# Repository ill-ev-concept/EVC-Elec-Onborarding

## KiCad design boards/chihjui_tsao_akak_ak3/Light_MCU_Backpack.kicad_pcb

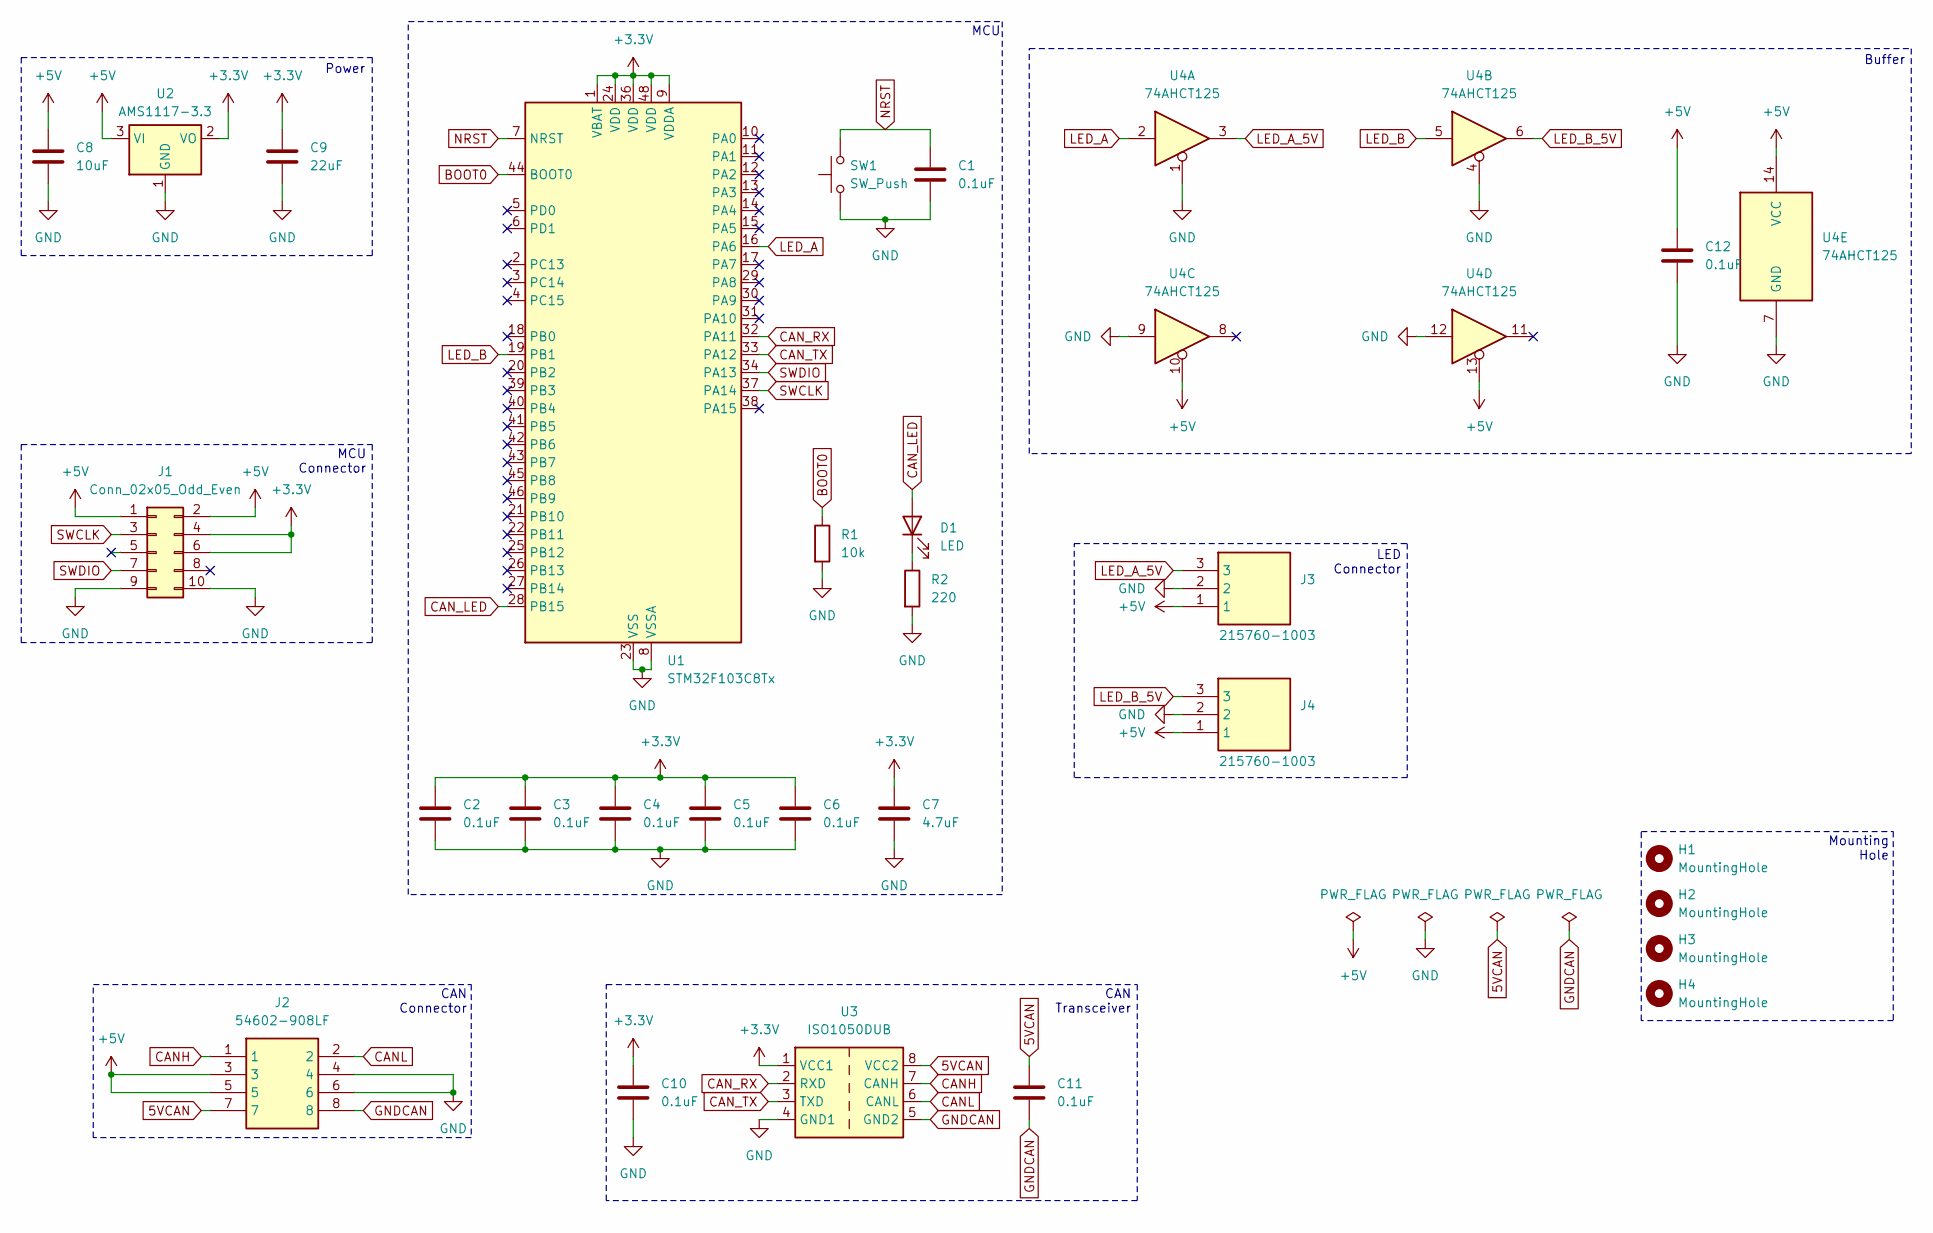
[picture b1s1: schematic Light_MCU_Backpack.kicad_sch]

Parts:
C1, C2, C3, C4, C5, C6, C10, C11, C12: 0.1uF; C_0805_2012Metric
C7: 4.7uF; C_0805_2012Metric
C8: 10uF; C_0805_2012Metric
C9: 22uF; C_0805_2012Metric
D1: LED; LED_0805_2012Metric
H1, H2, H3, H4: MountingHole; MountingHole_3.2mm_M3
J1: Conn_02x05_Odd_Even; PinSocket_2x05_P2.54mm_Vertical
J2: 54602-908LF; 54602908LF; Manufacturer_Part_Number 54602-908LF
J3, J4: 215760-1003; 215760-YY03; Mouser Part Number 538-215760-1003
R1: 10k; R_0805_2012Metric
R2: 220; R_0805_2012Metric
SW1: SW_Push; SW_SPST_EVQQ2
U1: STM32F103C8Tx; LQFP-48_7x7mm_P0.5mm
U2: AMS1117-3.3; SOT-223-3_TabPin2
U3: ISO1050DUB; SOP-8_6.62x9.15mm_P2.54mm
U4: 74AHCT125; SOIC-14_3.9x8.7mm_P1.27mm

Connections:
5VCAN: C11.2, J2.7, U3.8 (VCC2)
+3.3V: C2.1, C3.1, C4.1, C5.1, C6.1, C7.1, C9.2, C10.2, J1.4, J1.6, U1.1 (VBAT), U1.9 (VDDA), U1.24 (VDD), U1.36 (VDD), U1.48 (VDD), U2.2 (VO), U3.1 (VCC1)
+5V: C8.2, C12.1, J1.1, J1.2, J2.3, J2.5, J3.1, J4.1, U2.3 (VI), U4.10, U4.13, U4.14 (VCC)
BOOT0: R1.1, U1.44 (BOOT0)
CANH: J2.1, U3.7 (CANH)
CANL: J2.2, U3.6 (CANL)
CAN_LED: D1.2 (A), U1.28 (PB15)
CAN_RX: U1.32 (PA11), U3.2 (RXD)
CAN_TX: U1.33 (PA12), U3.3 (TXD)
GND: C1.2, C2.2, C3.2, C4.2, C5.2, C6.2, C7.2, C8.1, C9.1, C10.1, C12.2, J1.9, J1.10, J2.4, J2.6, J3.2, J4.2, R1.2, R2.2, SW1.1, U1.8 (VSSA), U1.23 (VSS), U1.35 (VSS), U1.47 (VSS), U2.1 (GND), U3.4 (GND1), U4.1, U4.4, U4.7 (GND), U4.9, U4.12
GNDCAN: C11.1, J2.8, U3.5 (GND2)
LED_A: U1.16 (PA6), U4.2
LED_A_5V: J3.3, U4.3
LED_B: U1.19 (PB1), U4.5
LED_B_5V: J4.3, U4.6
NRST: C1.1, SW1.2, U1.7 (NRST)
unnamed: D1.1 (K), R2.1
SWCLK: J1.3, U1.37 (PA14)
SWDIO: J1.7, U1.34 (PA13)

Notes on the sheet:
Power
CAN Transceiver
CAN Connector
Buffer
MCU Connector
Mounting Hole
LED Connector
MCU

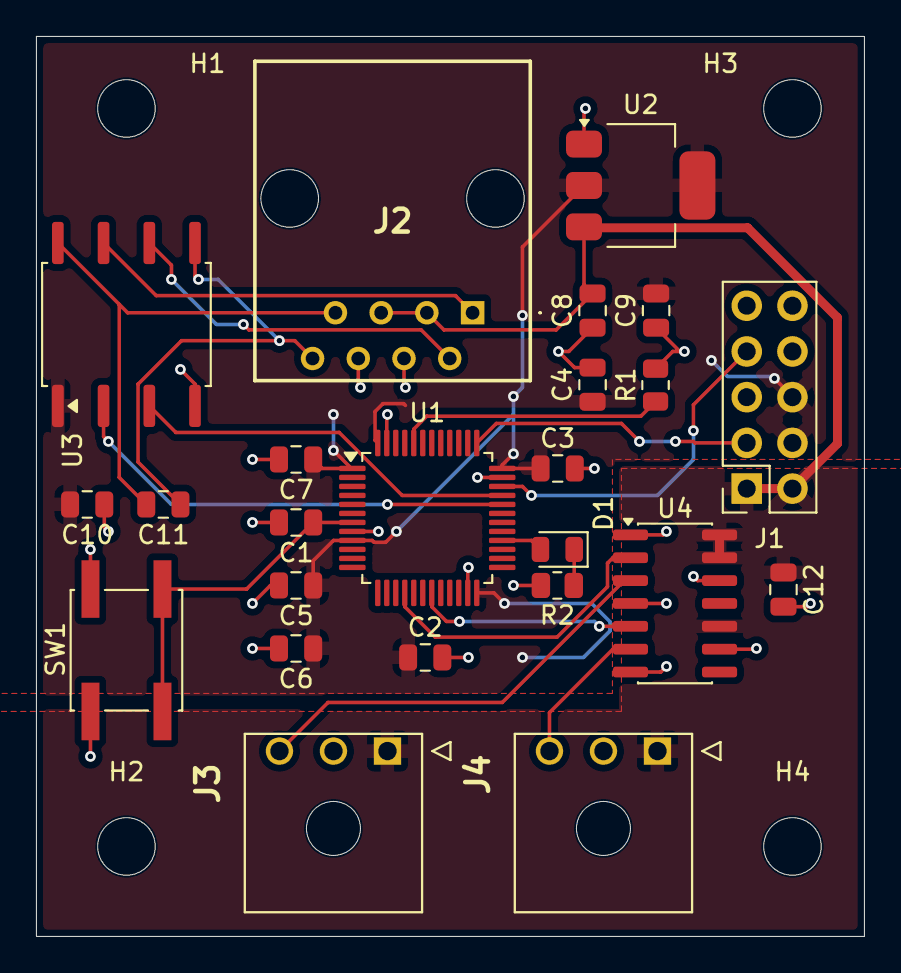
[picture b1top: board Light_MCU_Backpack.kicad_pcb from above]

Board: 2 copper layers, 46.0 x 50.0 mm, 28 parts (0 on the bottom side), 19 nets.

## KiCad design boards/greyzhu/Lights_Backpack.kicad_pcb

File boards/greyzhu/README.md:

# Lights Microcontroller Backpack

Two-layer STM32F103C8T6 board with isolated CAN and two buffered WS2812 interfaces.

| Item | Value |
|---|---|
| Contributor | greyzhu |
| GitHub | saffiotialfredo949-ctrl |
| Discord | grey077913 |
| KiCad | 10.0.6 |
| Board | 100 x 80 mm, two layers, 1.6 mm FR-4 |

## Open the project

Open `Lights_Backpack.kicad_pro` in KiCad. Keep the directory structure intact: the symbol library, footprint library and library tables use `${KIPRJMOD}` paths.

## Contents

- `Lights_Backpack.kicad_sch` and `Lights_Backpack.kicad_pcb`: schematic and routed PCB.
- `Lights_Backpack.pdf`: schematic preview.
- `Backpack.kicad_sym`, `Backpack.pretty/` and library tables: project libraries.
- `BOM.csv`: component list; blank MPN fields require purchasing selection.
- `Component_Positions_Reference.csv`: placement reference in KiCad absolute coordinates.
- `manufacturing/`: nine Gerbers, one Gerber job and two Excellon drill files.
- `ERC_Passed.rpt`, `DRC_Passed.rpt` and `Delivery_Checks.json`: design checks.
- `SHA256SUMS.txt`: file integrity manifest.
- [Hardware guide](HARDWARE_GUIDE.md): interfaces, power limits, fabrication details and initial test procedure.

## Validation and status

Native KiCad ERC reports zero errors and warnings. Native DRC reports zero violations, unconnected pads and footprint errors, with schematic parity enabled. These results apply to the configured checks; the reports list disabled categories.

The design is ready for team review. No prototype has been assembled or tested, and firmware is not included. Before fabrication or assembly, confirm the mating harness pinout, remaining component MPNs and system power budget. Each LED port targets at most 0.4 A before thermal and voltage derating. The CAN side requires an external isolated 5 V supply. J1 uses the custom team programming pinout.

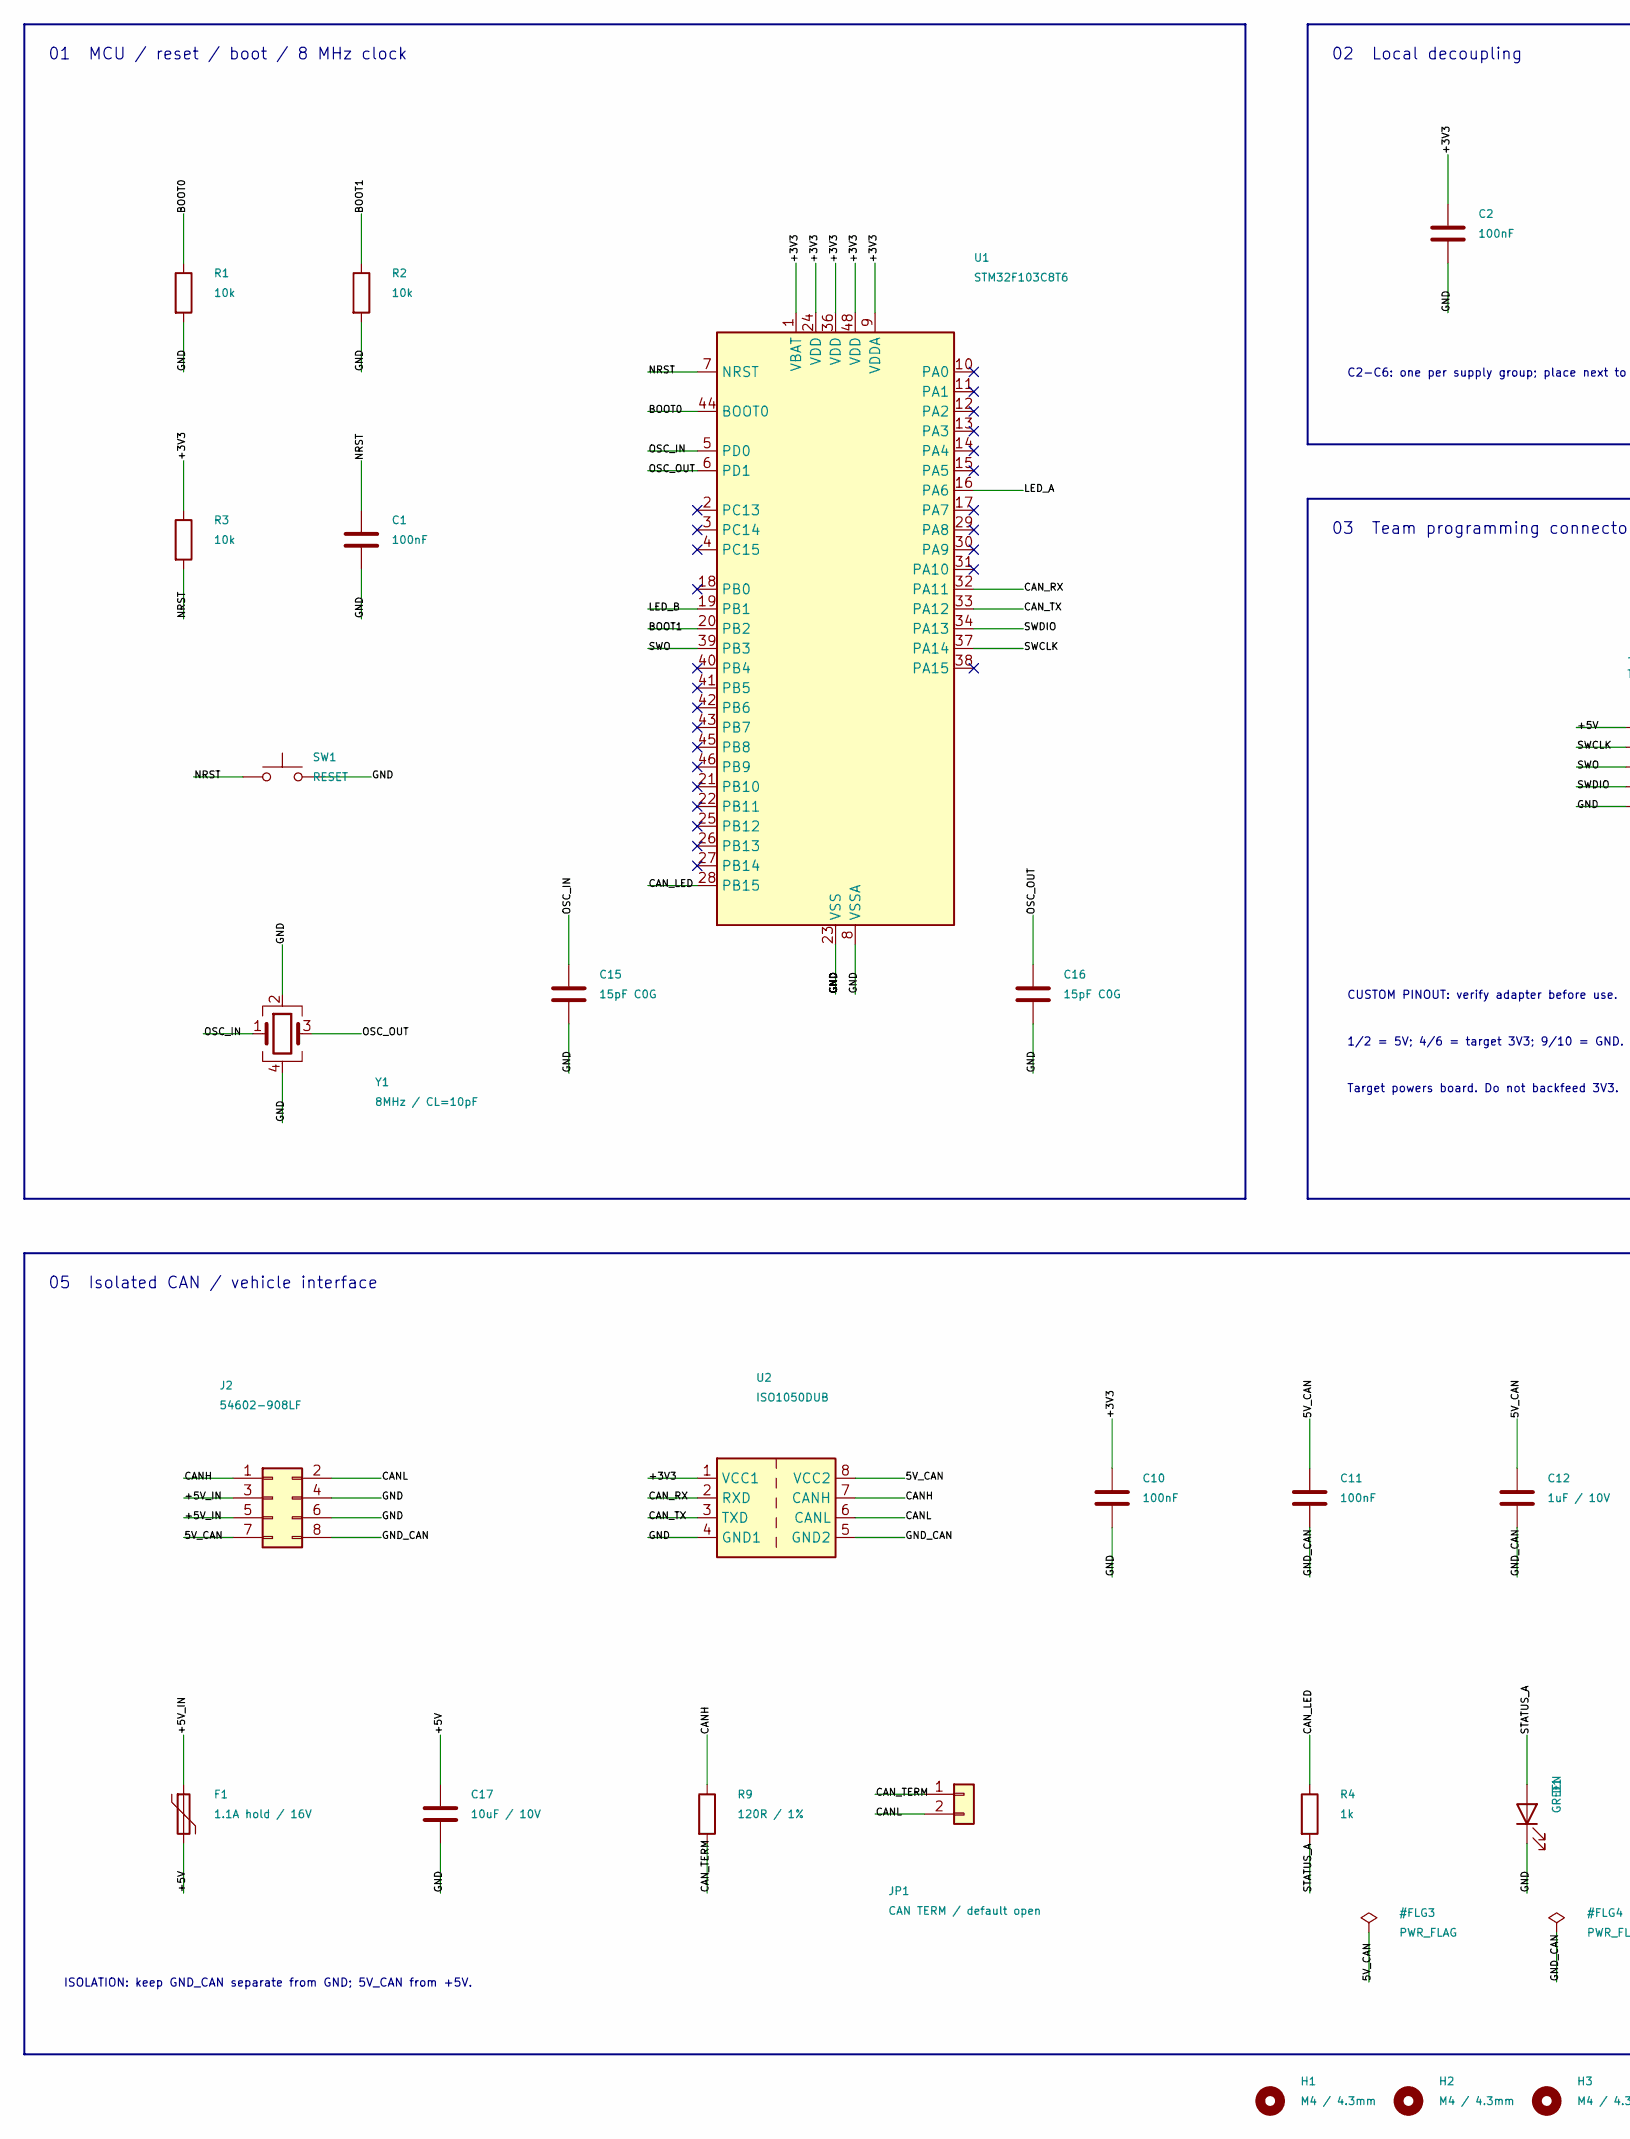
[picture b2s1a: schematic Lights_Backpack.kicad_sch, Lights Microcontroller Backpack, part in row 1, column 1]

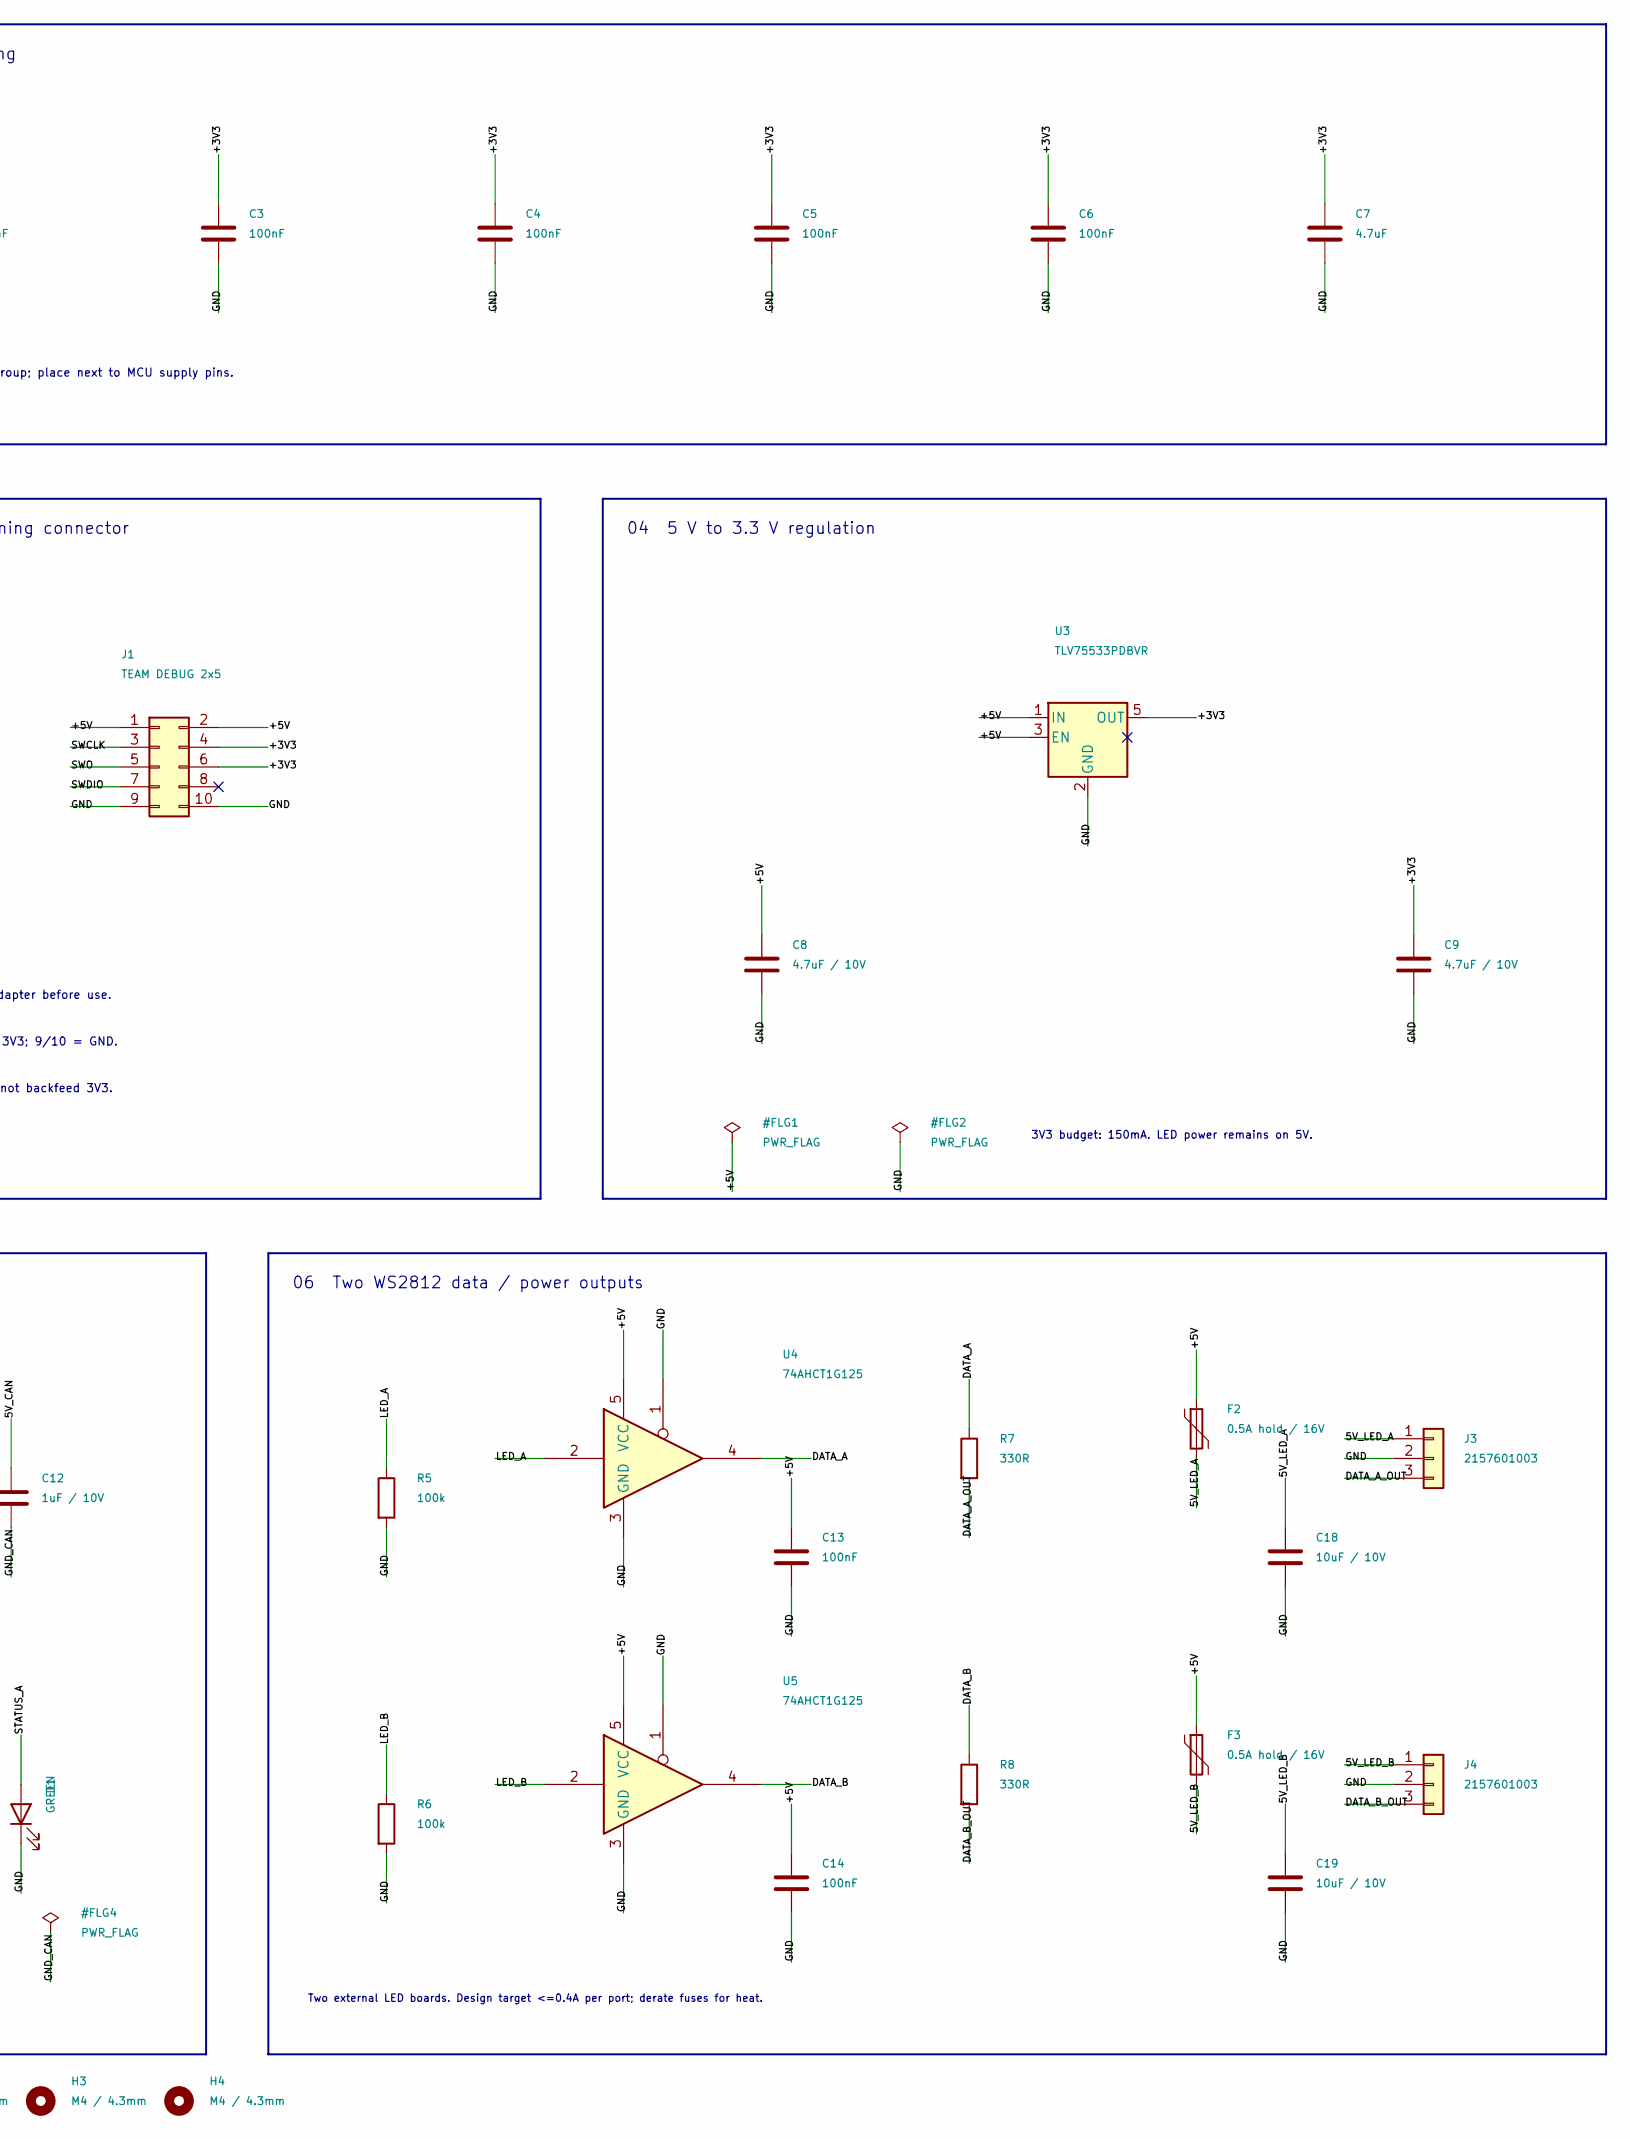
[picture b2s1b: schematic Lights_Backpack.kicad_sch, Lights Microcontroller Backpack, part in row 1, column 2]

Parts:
C1, C2, C3, C4, C5, C6, C10, C11, C13, C14: 100nF; C0603
C7: 4.7uF; C0805
C8, C9: 4.7uF / 10V; C0805
C12: 1uF / 10V; C0805
C15, C16: 15pF C0G; C0603
C17, C18, C19: 10uF / 10V; C0805
D1: GREEN; LED
F1: 1.1A hold / 16V; FUSE; MPN MF-MSMF110/16X-2
F2, F3: 0.5A hold / 16V; FUSE; MPN MF-MSMF050/16X-2
H1, H2, H3, H4: M4 / 4.3mm; HOLE
J1: TEAM DEBUG 2x5; DEBUG
J2: 54602-908LF; RJ45; MPN 54602-908LF
J3, J4: 2157601003; MICROFIT; MPN 2157601003
JP1: CAN TERM / default open; JUMPER
R1, R2, R3: 10k; R0603
R4: 1k; R0603
R5, R6: 100k; R0603
R7, R8: 330R; R0603
R9: 120R / 1%; R0805
SW1: RESET; SW
U1: STM32F103C8T6; MCU; MPN STM32F103C8T6
U2: ISO1050DUB; ISO; MPN ISO1050DUB
U3: TLV75533PDBVR; SOT5; MPN TLV75533PDBVR
U4, U5: 74AHCT1G125; SOT5; MPN SN74AHCT1G125DBVR
Y1: 8MHz / CL=10pF; CRYSTAL; MPN ABM3B-8.000MHZ-10-1-U-T

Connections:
/5V_CAN: C11.1, C12.1, J2.7, U2.8 (VCC2)
/5V_LED_A: C18.1, F2.2, J3.1
/5V_LED_B: C19.1, F3.2, J4.1
/+3V3: C2.1, C3.1, C4.1, C5.1, C6.1, C7.1, C9.1, C10.1, J1.4, J1.6, R3.1, U1.1 (VBAT), U1.9 (VDDA), U1.24 (VDD), U1.36 (VDD), U1.48 (VDD), U2.1 (VCC1), U3.5 (OUT)
/+5V: C8.1, C13.1, C14.1, C17.1, F1.2, F2.1, F3.1, J1.1, J1.2, U3.1 (IN), U3.3 (EN), U4.5 (VCC), U5.5 (VCC)
/+5V_IN: F1.1, J2.3, J2.5
/BOOT0: R1.1, U1.44 (BOOT0)
/BOOT1: R2.1, U1.20 (PB2)
/CANH: J2.1, R9.1, U2.7 (CANH)
/CANL: J2.2, JP1.2, U2.6 (CANL)
/CAN_LED: R4.1, U1.28 (PB15)
/CAN_RX: U1.32 (PA11), U2.2 (RXD)
/CAN_TERM: JP1.1, R9.2
/CAN_TX: U1.33 (PA12), U2.3 (TXD)
/DATA_A: R7.1, U4.4
/DATA_A_OUT: J3.3, R7.2
/DATA_B: R8.1, U5.4
/DATA_B_OUT: J4.3, R8.2
/GND: C1.2, C2.2, C3.2, C4.2, C5.2, C6.2, C7.2, C8.2, C9.2, C10.2, C13.2, C14.2, C15.2, C16.2, C17.2, C18.2, C19.2, D1.1 (K), J1.9, J1.10, J2.4, J2.6, J3.2, J4.2, R1.2, R2.2, R5.2, R6.2, SW1.2, U1.8 (VSSA), U1.23 (VSS), U1.35 (VSS), U1.47 (VSS), U2.4 (GND1), U3.2 (GND), U4.1, U4.3 (GND), U5.1, U5.3 (GND), Y1.2, Y1.4
/GND_CAN: C11.2, C12.2, J2.8, U2.5 (GND2)
/LED_A: R5.1, U1.16 (PA6), U4.2
/LED_B: R6.1, U1.19 (PB1), U5.2
/NRST: C1.1, R3.2, SW1.1, U1.7 (NRST)
/OSC_IN: C15.1, U1.5 (PD0), Y1.1
/OSC_OUT: C16.1, U1.6 (PD1), Y1.3
/STATUS_A: D1.2 (A), R4.2
/SWCLK: J1.3, U1.37 (PA14)
/SWDIO: J1.7, U1.34 (PA13)
/SWO: J1.5, U1.39 (PB3)

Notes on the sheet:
06 Two WS2812 data / power outputs
Target powers board. Do not backfeed 3V3.
02 Local decoupling
01 MCU / reset / boot / 8 MHz clock
1/2 = 5V; 4/6 = target 3V3; 9/10 = GND.
C2-C6: one per supply group; place next to MCU supply pins.
Two external LED boards. Design target <=0.4A per port; derate fuses for heat.
05 Isolated CAN / vehicle interface
04 5 V to 3.3 V regulation
03 Team programming connector
ISOLATION: keep GND_CAN separate from GND; 5V_CAN from +5V.
3V3 budget: 150mA. LED power remains on 5V.
CUSTOM PINOUT: verify adapter before use.

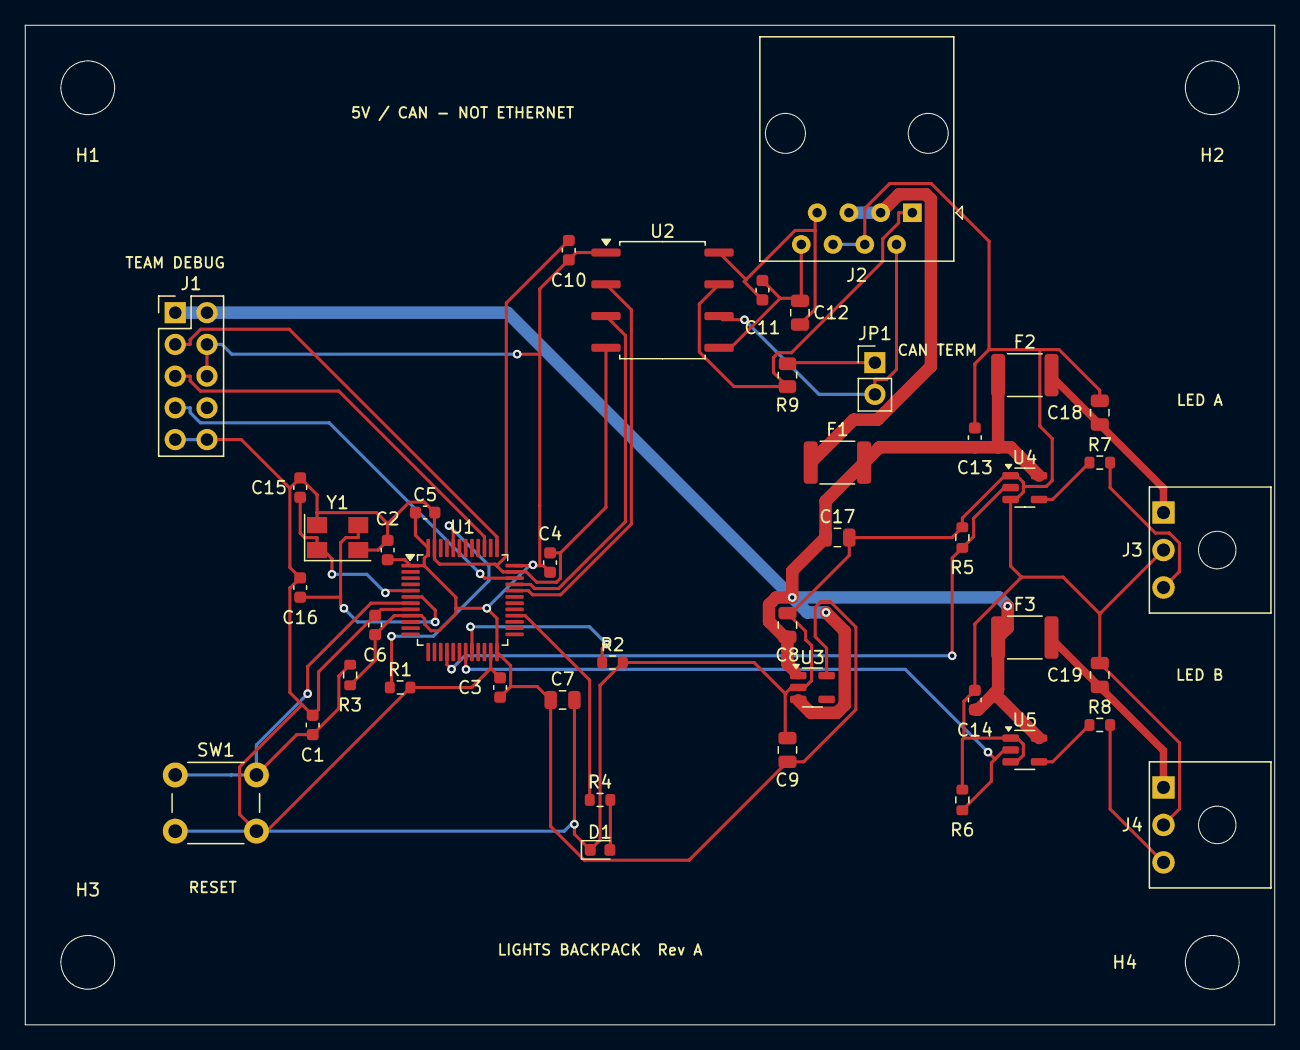
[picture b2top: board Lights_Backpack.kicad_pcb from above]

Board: 2 copper layers, 100.0 x 80.0 mm, 48 parts (0 on the bottom side), 29 nets.

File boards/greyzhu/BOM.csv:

Reference,Quantity,Value,MPN,Footprint,Design note
C1,1,100nF,,Backpack:C0603,
C2,1,100nF,,Backpack:C0603,
C3,1,100nF,,Backpack:C0603,
C4,1,100nF,,Backpack:C0603,
C5,1,100nF,,Backpack:C0603,
C6,1,100nF,,Backpack:C0603,
C7,1,4.7uF,,Backpack:C0805,
C8,1,4.7uF / 10V,,Backpack:C0805,
C9,1,4.7uF / 10V,,Backpack:C0805,
C10,1,100nF,,Backpack:C0603,
C11,1,100nF,,Backpack:C0603,
C12,1,1uF / 10V,,Backpack:C0805,
C13,1,100nF,,Backpack:C0603,
C14,1,100nF,,Backpack:C0603,
C15,1,15pF C0G,,Backpack:C0603,
C16,1,15pF C0G,,Backpack:C0603,
C17,1,10uF / 10V,,Backpack:C0805,
C18,1,10uF / 10V,,Backpack:C0805,
C19,1,10uF / 10V,,Backpack:C0805,
D1,1,GREEN,,Backpack:LED,
F1,1,1.1A hold / 16V,MF-MSMF110/16X-2,Backpack:FUSE,
F2,1,0.5A hold / 16V,MF-MSMF050/16X-2,Backpack:FUSE,
F3,1,0.5A hold / 16V,MF-MSMF050/16X-2,Backpack:FUSE,
H1,1,M4 / 4.3mm,,Backpack:HOLE,4.3mm non-plated mounting hole; keep copper clear.
H2,1,M4 / 4.3mm,,Backpack:HOLE,4.3mm non-plated mounting hole; keep copper clear.
H3,1,M4 / 4.3mm,,Backpack:HOLE,4.3mm non-plated mounting hole; keep copper clear.
H4,1,M4 / 4.3mm,,Backpack:HOLE,4.3mm non-plated mounting hole; keep copper clear.
J1,1,TEAM DEBUG 2x5,,Backpack:DEBUG,Custom team pinout. Not ARM Cortex 10-pin. Do not parallel external 5V sources.
J2,1,54602-908LF,54602-908LF,Backpack:RJ45,"Team vehicle connector, NOT Ethernet. Pinout from assignment."
J3,1,2157601003,2157601003,Backpack:MICROFIT,"Board pinout: 1=5V, 2=GND, 3=DATA. Confirm mating harness."
J4,1,2157601003,2157601003,Backpack:MICROFIT,"Board pinout: 1=5V, 2=GND, 3=DATA. Confirm mating harness."
JP1,1,CAN TERM / default open,,Backpack:JUMPER,Default open. Fit only if this node is one of the two physical bus ends.
R1,1,10k,,Backpack:R0603,
R2,1,10k,,Backpack:R0603,
R3,1,10k,,Backpack:R0603,
R4,1,1k,,Backpack:R0603,
R5,1,100k,,Backpack:R0603,
R6,1,100k,,Backpack:R0603,
R7,1,330R,,Backpack:R0603,
R8,1,330R,,Backpack:R0603,
R9,1,120R / 1%,,Backpack:R0805,
SW1,1,RESET,,Backpack:SW,
U1,1,STM32F103C8T6,STM32F103C8T6,Backpack:MCU,
U2,1,ISO1050DUB,ISO1050DUB,Backpack:ISO,
U3,1,TLV75533PDBVR,TLV75533PDBVR,Backpack:SOT5,
U4,1,74AHCT1G125,SN74AHCT1G125DBVR,Backpack:SOT5,
U5,1,74AHCT1G125,SN74AHCT1G125DBVR,Backpack:SOT5,
Y1,1,8MHz / CL=10pF,ABM3B-8.000MHZ-10-1-U-T,Backpack:CRYSTAL,

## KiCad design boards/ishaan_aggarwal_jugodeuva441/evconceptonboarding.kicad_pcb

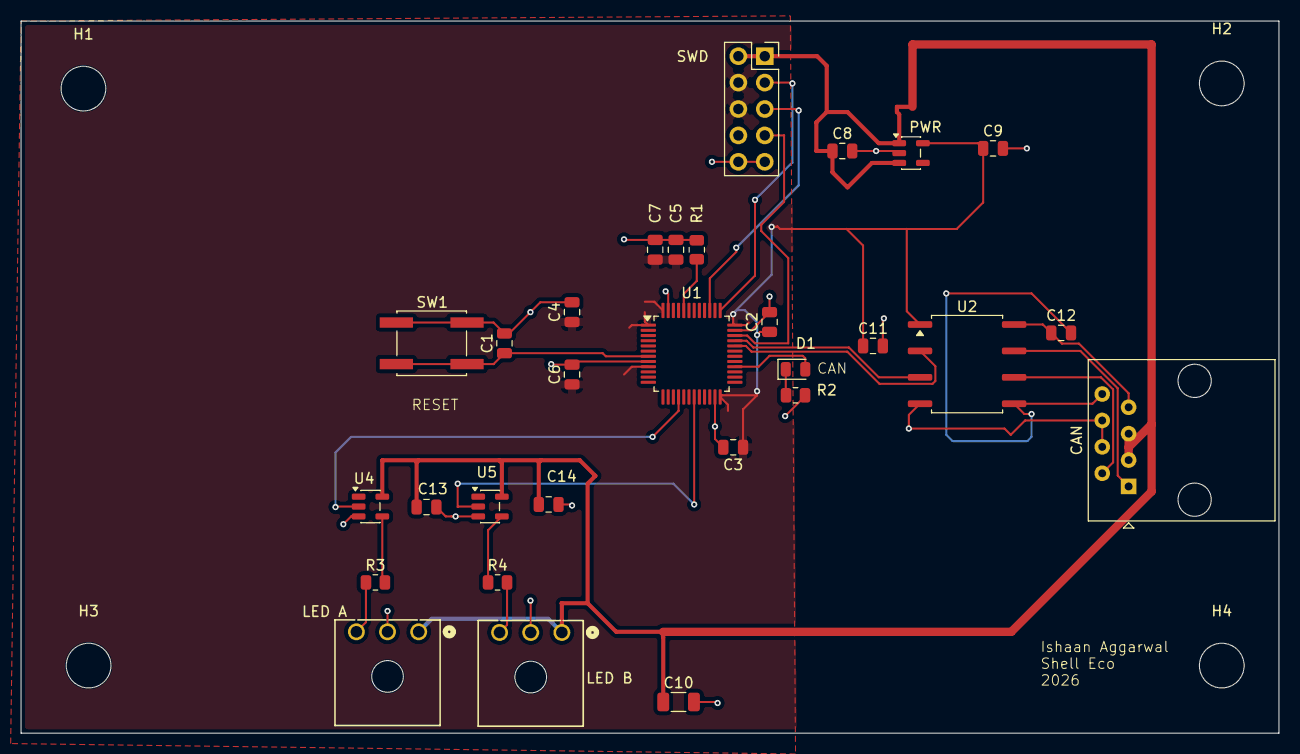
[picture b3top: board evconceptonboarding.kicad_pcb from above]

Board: 2 copper layers, 121.0 x 68.5 mm, 33 parts (0 on the bottom side), 22 nets.

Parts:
C1, C2, C3, C4, C5, C6, C11, C12, C13, C14: 100nf; C_0805_2012Metric
C7: 4.7 uf; C_0805_2012Metric
C8, C9: 1 uf; C_0805_2012Metric
C10: 22uF; C_1206_3216Metric
CAN: 54602-908LF; RJ45_Amphenol_54602-x08_Horizontal
D1: LED; LED_0805_2012Metric
H1, H2, H3, H4: MountingHole; MountingHole_4.3mm_M4
LED A: 2157601003; CONN_2157600003-SD_03_PEG_MOL
LED B: 2157601003; CONN_2157600003-SD_03_PEG_MOL
PWR: AP2112K-3.3; SOT-23-5
R1: 10k ohm; R_0805_2012Metric
R2: 220 Ohm; R_0805_2012Metric
R3, R4: 330 Ohm; R_0805_2012Metric
SW1: SW_Push; SW_SPST_EVQQ2
SWD: Conn_02x05_Odd_Even; PinSocket_2x05_P2.54mm_Vertical
U1: STM32F103C8Tx; LQFP-48_7x7mm_P0.5mm
U2: ISO1050DUB; SOP-8_6.62x9.15mm_P2.54mm
U4, U5: SN74LV1T34DBV; SOT-23-5

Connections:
5V_CAN: C12.1, CAN.7, U2.8 (VCC2)
+3.3V: C2.1, C3.1, C4.1, C5.1, C6.1, C7.1, C9.1, C11.1, PWR.5 (VOUT), SWD.4, SWD.6, U1.1 (VBAT), U1.9 (VDDA), U1.24 (VDD), U1.36 (VDD), U1.48 (VDD), U2.1 (VCC1)
+5V: C8.1, C10.1, C13.1, C14.1, CAN.3, CAN.5, LED A.1, LED B.1, PWR.1 (VIN), PWR.3 (EN), SWD.1, SWD.2, U4.5 (VCC), U5.5 (VCC)
BOOT0: R1.1, U1.44 (BOOT0)
CANRX: U1.32 (PA11), U2.2 (RXD)
CANTX: U1.33 (PA12), U2.3 (TXD)
CAN_HIGH: CAN.1, U2.7 (CANH)
CAN_LED: D1.2 (A), U1.28 (PB15)
CAN_LOW: CAN.2, U2.6 (CANL)
GND: C1.2, C2.2, C3.2, C4.2, C5.2, C6.2, C7.2, C8.2, C9.2, C10.2, C11.2, C13.2, C14.2, CAN.4, CAN.6, LED A.2, LED B.2, PWR.2 (GND), R1.2, R2.2, SW1.1, SWD.9, SWD.10, U1.8 (VSSA), U1.23 (VSS), U1.35 (VSS), U1.47 (VSS), U2.4 (GND1), U4.3 (GND), U5.3 (GND)
GND_CAN: C12.2, CAN.8, U2.5 (GND2)
LED_A: U1.16 (PA6), U4.2 (A)
LED_A_5V: LED A.3, R3.1
LED_B: U1.19 (PB1), U5.2 (A)
LED_B_5V: LED B.3, R4.2
NRST: C1.1, SW1.2, U1.7 (NRST)
unnamed: D1.1 (K), R2.1
unnamed: R3.2, U4.4 (Y)
unnamed: R4.1, U5.4 (Y)
SWCLK: SWD.3, U1.37 (PA14)
SWDIO: SWD.7, U1.34 (PA13)
SWO: SWD.5, U1.39 (PB3)

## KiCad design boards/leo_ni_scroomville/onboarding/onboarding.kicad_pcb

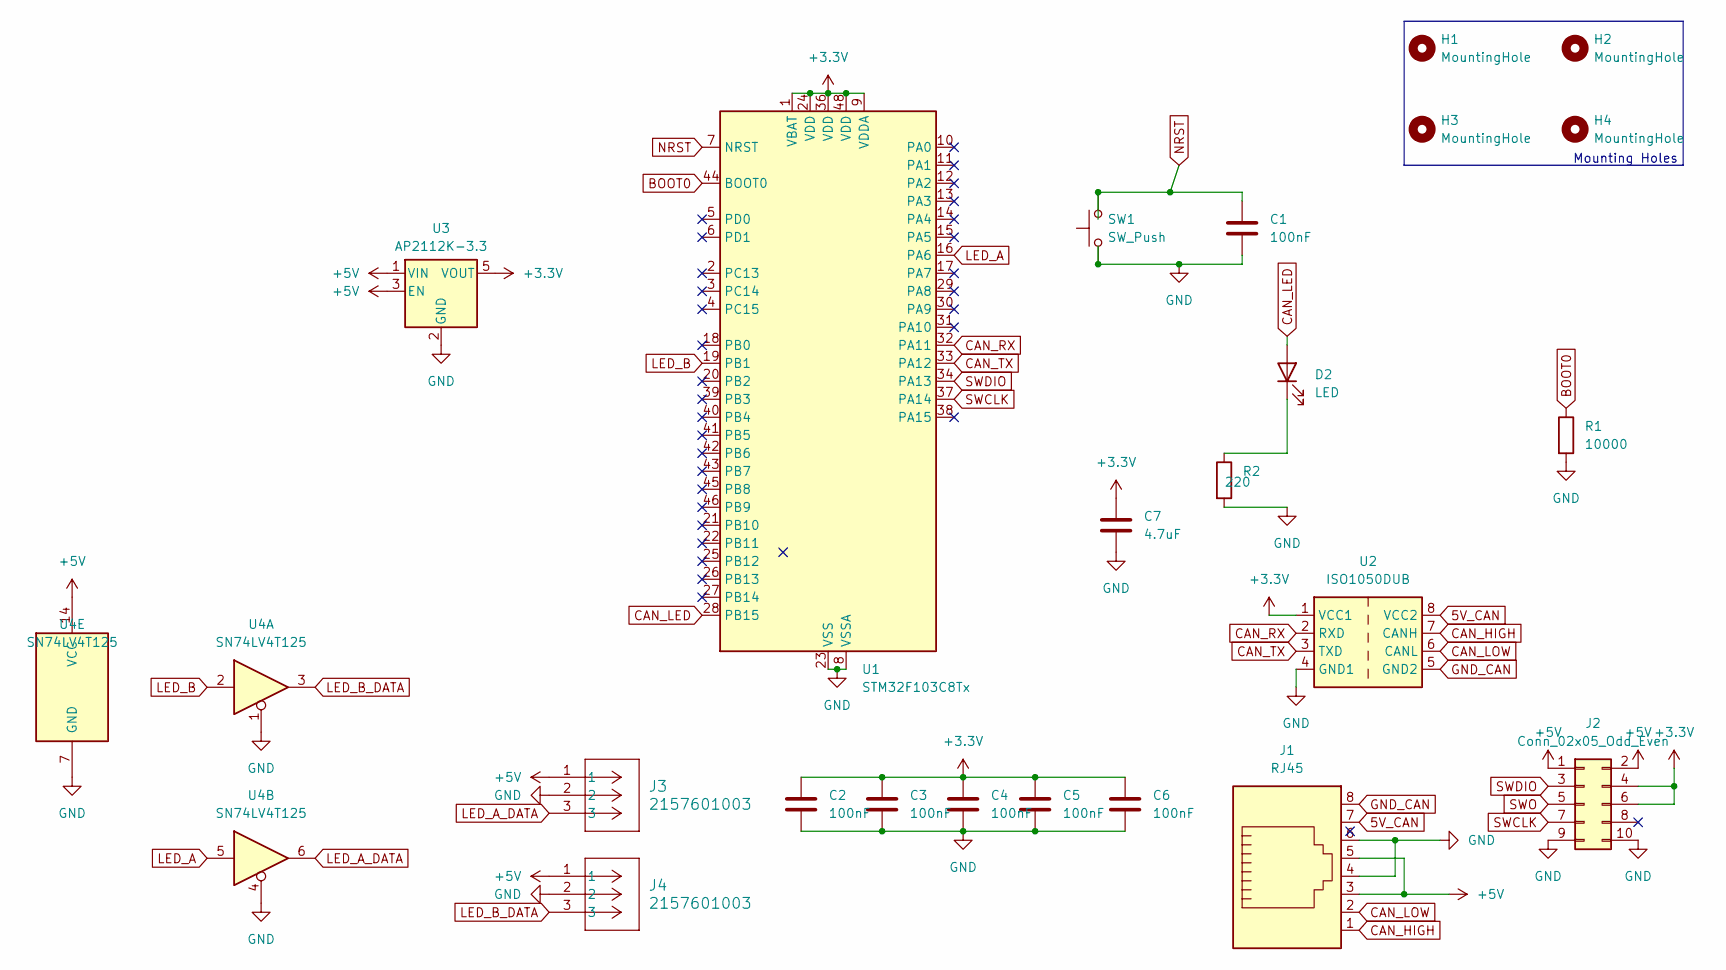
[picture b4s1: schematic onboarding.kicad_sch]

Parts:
C1, C2, C3, C4, C5, C6: 100nF; C_0805_2012Metric
C7: 4.7uF; C_0805_2012Metric
D2: LED; LED_0805_2012Metric
H1, H2, H3, H4: MountingHole; MountingHole_3.2mm_M3
J1: RJ45; CONN8_2-908LF_AMP
J2: Conn_02x05_Odd_Even; PinSocket_2x05_P2.54mm_Vertical
J3, J4: 2157601003; CONN_2157600003-SD_03_PEG_MOL
R1: 10000; R_0805_2012Metric
R2: 220; R_0805_2012Metric
SW1: SW_Push; SW_SPST_EVQQ2
U1: STM32F103C8Tx; LQFP-48_7x7mm_P0.5mm
U2: ISO1050DUB; SOP-8_6.62x9.15mm_P2.54mm
U3: AP2112K-3.3; SOT-23-5
U4: SN74LV4T125; TSSOP-14_4.4x5mm_P0.65mm

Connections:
5V_CAN: J1.7, U2.8 (VCC2)
+3.3V: C2.1, C3.1, C4.1, C5.1, C6.1, C7.1, J2.4, J2.6, U1.1 (VBAT), U1.9 (VDDA), U1.24 (VDD), U1.36 (VDD), U1.48 (VDD), U2.1 (VCC1), U3.5 (VOUT)
+5V: J1.3, J1.5, J2.1, J2.2, J3.1, J4.1, U3.1 (VIN), U3.3 (EN), U4.14 (VCC)
BOOT0: R1.1, U1.44 (BOOT0)
CAN_HIGH: J1.1, U2.7 (CANH)
CAN_LED: D2.2 (A), U1.28 (PB15)
CAN_LOW: J1.2, U2.6 (CANL)
CAN_RX: U1.32 (PA11), U2.2 (RXD)
CAN_TX: U1.33 (PA12), U2.3 (TXD)
GND: C1.2, C2.2, C3.2, C4.2, C5.2, C6.2, C7.2, J1.4, J1.6, J2.9, J2.10, J3.2, J4.2, R1.2, R2.2, SW1.1, U1.8 (VSSA), U1.23 (VSS), U1.35 (VSS), U1.47 (VSS), U2.4 (GND1), U3.2 (GND), U4.1, U4.4, U4.7 (GND)
GND_CAN: J1.8, U2.5 (GND2)
LED_A: U1.16 (PA6), U4.5
LED_A_DATA: J3.3, U4.6
LED_B: U1.19 (PB1), U4.2
LED_B_DATA: J4.3, U4.3
NRST: C1.1, SW1.2, U1.7 (NRST)
unnamed: D2.1 (K), R2.1
SWCLK: J2.7, U1.37 (PA14)
SWDIO: J2.3, U1.34 (PA13)
SWO: J2.5

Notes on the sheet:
Mounting Holes

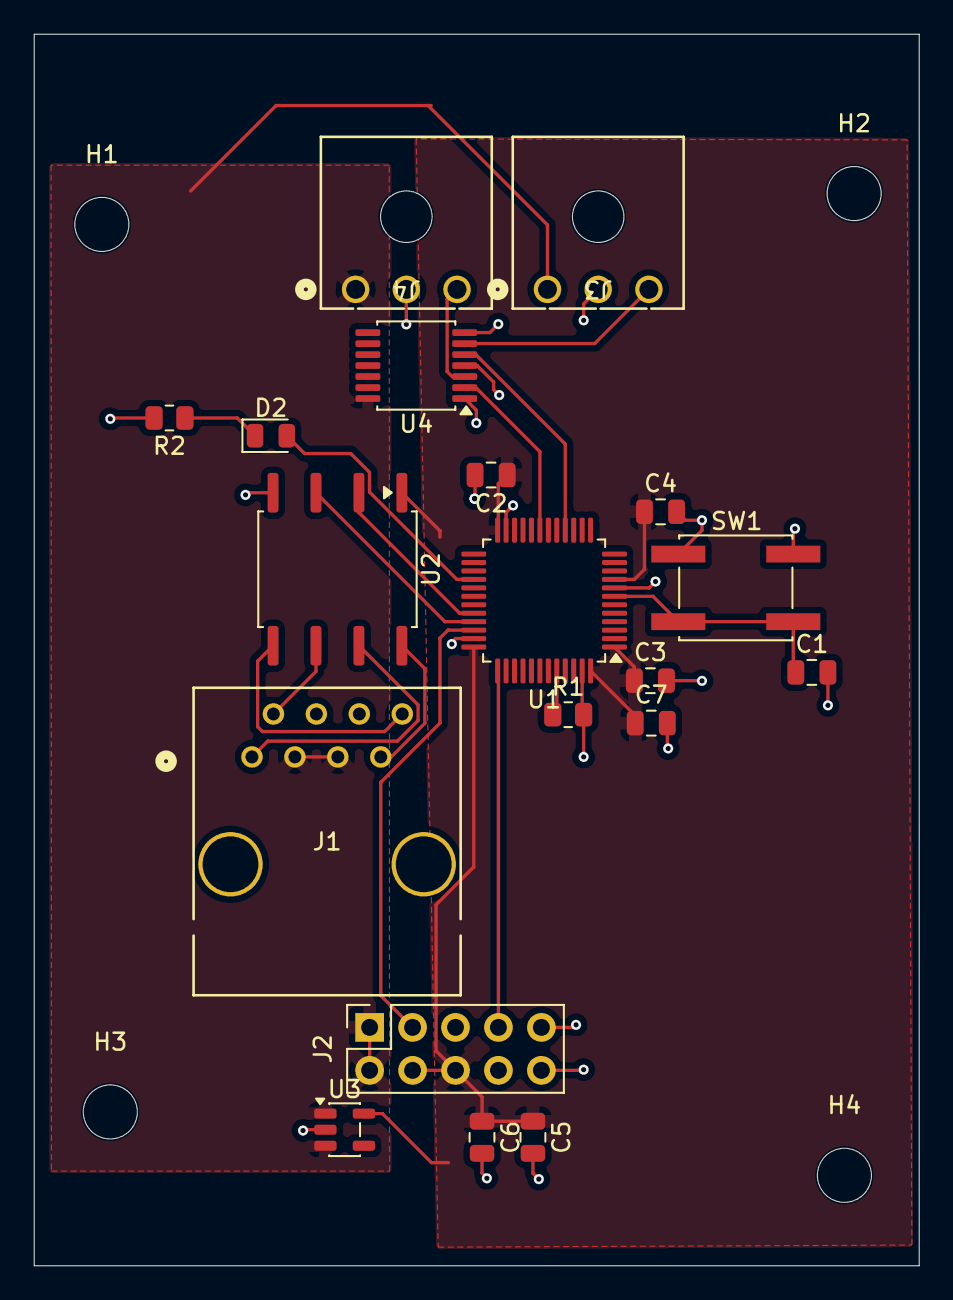
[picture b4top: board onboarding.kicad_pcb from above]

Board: 2 copper layers, 52.4 x 72.8 mm, 24 parts (0 on the bottom side), 19 nets.

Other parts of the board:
H4#2: MountingHole; MountingHole_3.2mm_M3
